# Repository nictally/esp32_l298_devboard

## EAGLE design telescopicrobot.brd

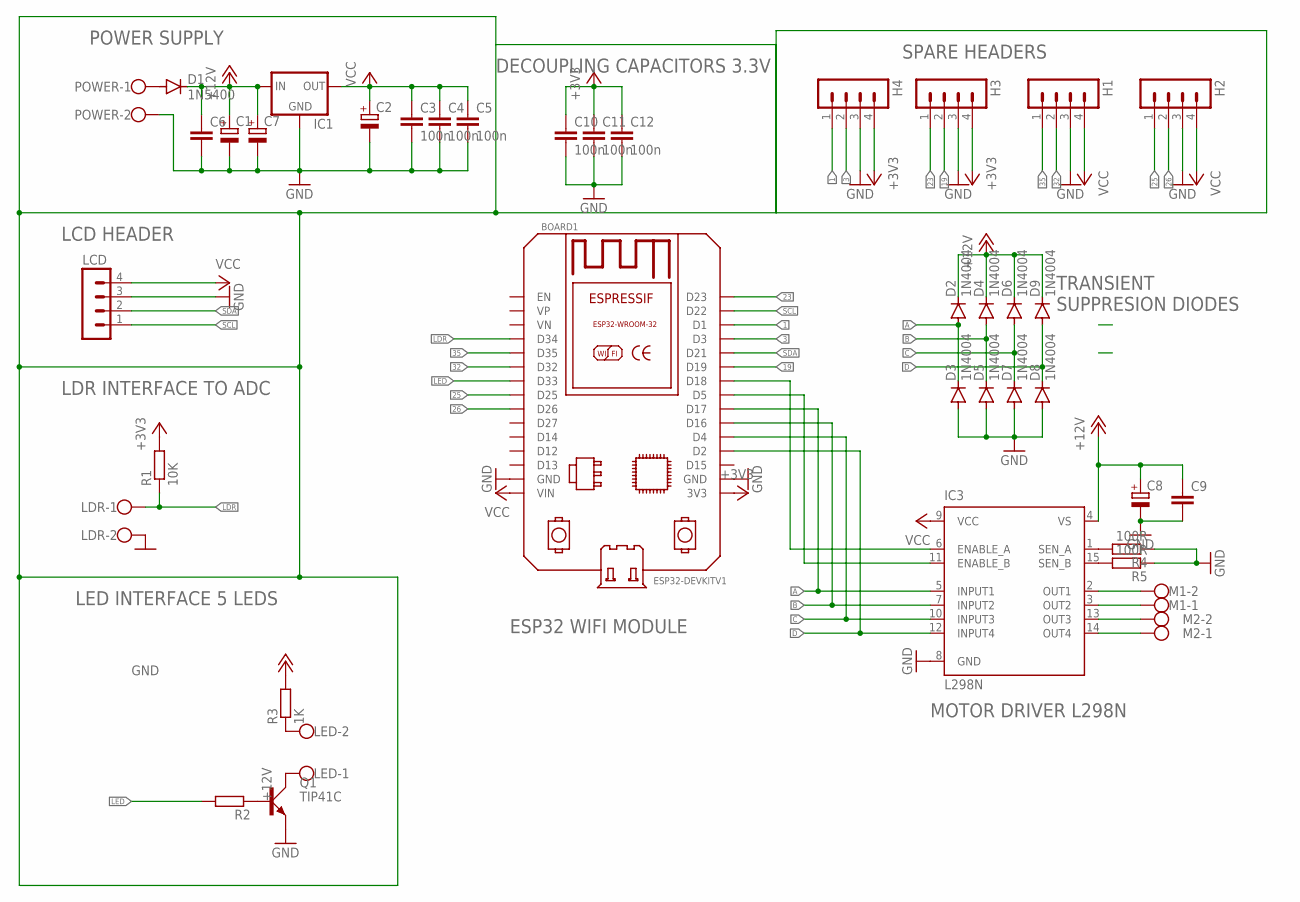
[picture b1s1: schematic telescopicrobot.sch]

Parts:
BOARD1: ESP32DEVKITV1; ESP32-DEVKITV1
C1, C7, C8: CPOL-EUE5-10.5; E5-10,5
C2: CPOL-EUE2.5-5; E2,5-5
C3, C4, C5, C10, C11, C12: 100n; C2.5-3
C6, C9: C2,5-3; C2.5-3
D1: 1N5400; DO201-15
D2, D3, D4, D5, D6, D7, D8, D9: 1N4004; DO41-10
H1, H2, H3, H4: MA04-1
IC1: 78XXS
IC3: L298N; MULTIWATT-15
LCD: MA04-1
LDR: W237-102
LED: W237-102
M1, M2: W237-102
POWER: W237-102
Q1: TIP41C; TO220AV
R1: 10K; 0207/12
R2: R-EU_0207/12; 0207/12
R3: 1K; 0207/12
R4, R5: 100R; 0207/12

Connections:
1: BOARD1.D1, H4.1
3: BOARD1.D3, H4.2
19: BOARD1.D19, H3.2
23: BOARD1.D23, H3.1
25: BOARD1.D25, H2.1
26: BOARD1.D26, H2.2
32: BOARD1.D32, H1.2
35: BOARD1.D35, H1.1
+3V3: BOARD1.3V3, C10.1, C11.1, C12.1, H3.4, H4.4, R1.2
+12V: C1.+, C6.1, C7.+, C8.+, C9.1, D1.C, D2.C, D4.C, D6.C, D9.C, IC1.IN, IC3.4 (VS), R3.2
A: BOARD1.D17, D2.A, D3.C, IC3.5 (INPUT1)
B: BOARD1.D16, D4.A, D5.C, IC3.7 (INPUT2)
C: BOARD1.D4, D6.A, D7.C, IC3.10 (INPUT3)
D: BOARD1.D2, D8.C, D9.A, IC3.12 (INPUT4)
GND: BOARD1.GND, BOARD1.GND@1 (GND), C1.-, C2.-, C3.2, C4.2, C5.2, C6.2, C7.-, C8.-, C9.2, C10.2, C11.2, C12.2, D3.A, D5.A, D7.A, D8.A, H1.3, H2.3, H3.3, H4.3, IC1.GND, IC3.8 (GND), LCD.3, LDR.2, POWER.2, Q1.E, R4.1, R5.1
LDR: BOARD1.D34, LDR.1, R1.1
LED: BOARD1.D33, R2.2
unnamed: LED.1, Q1.C
unnamed: IC3.3 (OUT2), M1.1
unnamed: IC3.2 (OUT1), M1.2
unnamed: IC3.14 (OUT4), M2.1
unnamed: IC3.13 (OUT3), M2.2
unnamed: Q1.B, R2.1
unnamed: BOARD1.D18, IC3.6 (ENABLE_A)
unnamed: D1.A, POWER.1
unnamed: LED.2, R3.1
unnamed: BOARD1.D5, IC3.11 (ENABLE_B)
unnamed: IC3.1 (SEN_A), R4.2
unnamed: IC3.15 (SEN_B), R5.2
SCL: BOARD1.D22, LCD.1
SDA: BOARD1.D21, LCD.2
VCC: BOARD1.VIN, C2.+, C3.1, C4.1, C5.1, H1.4, H2.4, IC1.OUT, IC3.9 (VCC), LCD.4

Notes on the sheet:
POWER SUPPLY
LCD HEADER
LDR INTERFACE TO ADC
LED INTERFACE 5 LEDS
ESP32 WIFI MODULE
MOTOR DRIVER L298N
TRANSIENT SUPPRESION DIODES
SPARE HEADERS
DECOUPLING CAPACITORS 3.3V

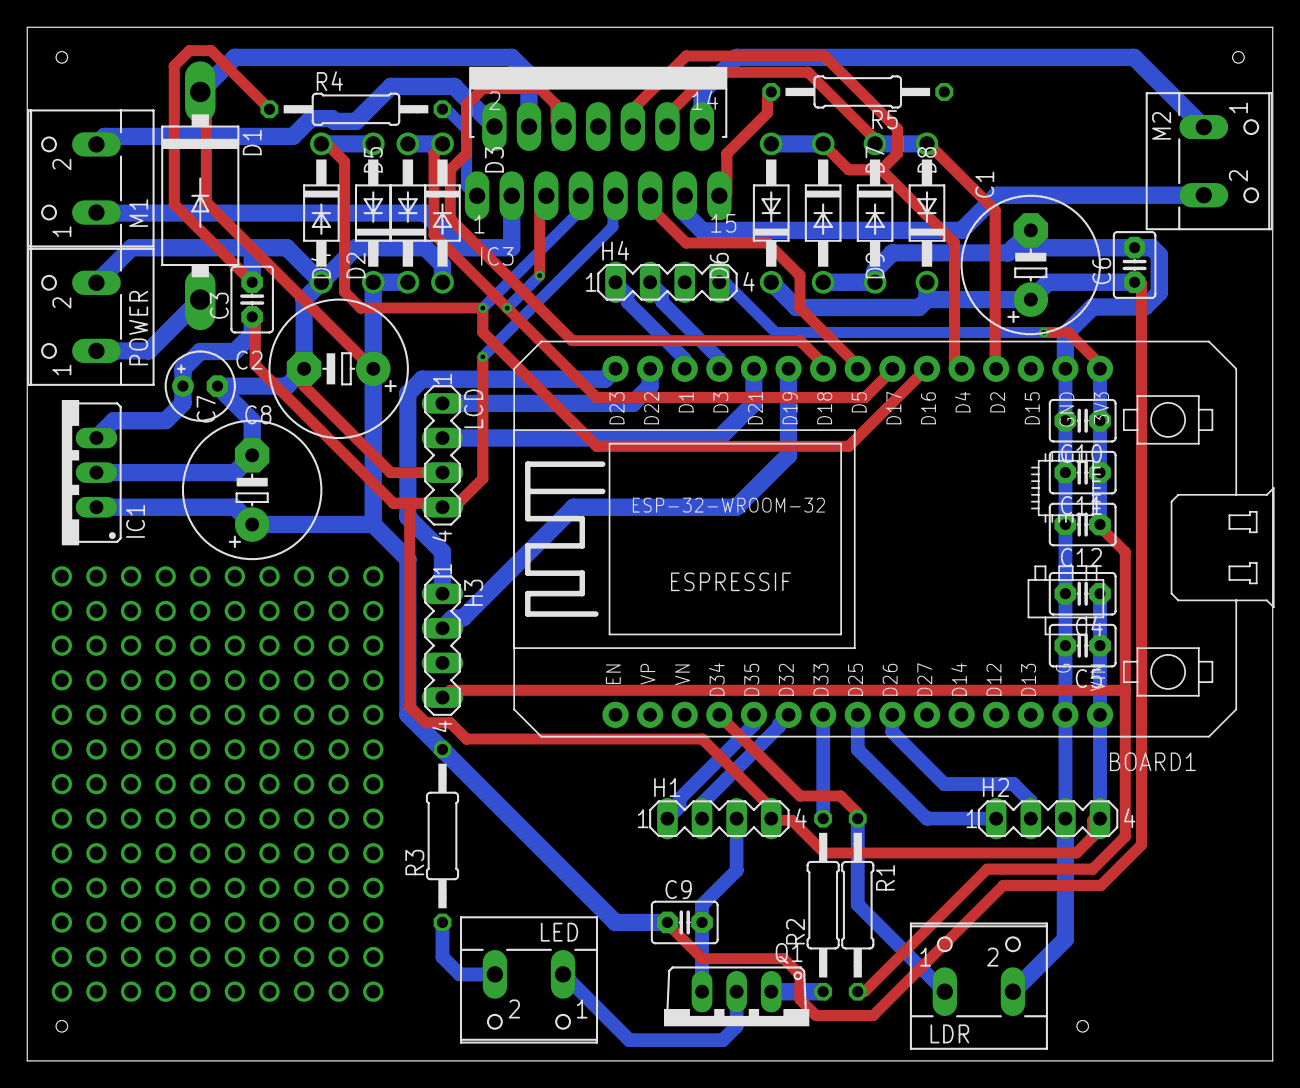
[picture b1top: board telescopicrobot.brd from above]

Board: 2 copper layers, 91.4 x 75.9 mm, 40 parts (0 on the bottom side), 32 nets.
